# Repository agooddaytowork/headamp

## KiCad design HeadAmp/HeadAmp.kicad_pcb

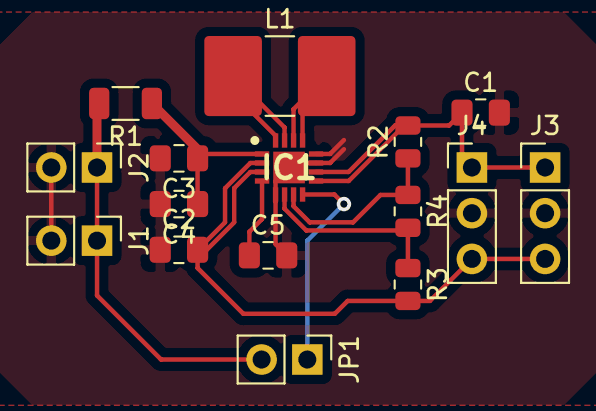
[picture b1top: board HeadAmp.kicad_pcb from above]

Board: 2 copper layers, 16 parts (0 on the bottom side), 11 nets.

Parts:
C1, C2, C3, C4, C5: C; C_0805_2012Metric_Pad1.18x1.45mm_HandSolder
IC1: TPS65135RTER; QFN50P300X300X80-17N-D
J1, J2: Conn_01x02_Female; PinHeader_1x02_P2.54mm_Vertical
J3: V+; PinHeader_1x03_P2.54mm_Vertical
J4: Conn_01x03_Female; PinHeader_1x03_P2.54mm_Vertical
JP1: Jumper; PinHeader_1x02_P2.54mm_Vertical
L1: INDUCTOR; L_2816_7142Metric_Pad3.20x4.45mm_HandSolder
R1: 0.0; R_1206_3216Metric
R2, R3, R4: R; R_0805_2012Metric

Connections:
+3.3V: J1.1, J2.1, JP1.2, R1.2
FB: IC1.7, R2.1, R4.1
FBG: IC1.6, R3.1, R4.2
GND: C1.2, C2.1, C3.2, C4.2, C5.2, IC1.5, IC1.11, IC1.12, IC1.17, J1.2, J2.2, J3.2, J4.2
unnamed: C3.1, C4.1, IC1.1, R1.1
unnamed: C5.1, IC1.4
unnamed: IC1.8, JP1.1
unnamed: IC1.13, IC1.14, L1.2
unnamed: IC1.15, IC1.16, L1.1
VCC+: C1.1, IC1.9, IC1.10, J3.1, J4.1, R2.2
VCC-: C2.2, IC1.2, IC1.3, J3.3, J4.3, R3.2

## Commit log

2021-03-22 1st commit
